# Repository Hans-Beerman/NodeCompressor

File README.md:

**NodeCompressor**

NodeCompressor is a node, used at the MakerSpace Leiden, to control the main compressor. This repository has the following subdirs:

- **Drawings:**

Schematic of the wiring between the different modules used

- **KiCad\_files:**

The design of the PCB for the Node/Controller. De PCB in this design is not meant to be used for a real PCB. It is used as guideline for a handmade PCB

- **Photos:**

Some photos of the Node made.

- **PlatformIO\_Files:**

The source code for the Node and the display used. For the development of this software PlatformIO is used, an Extension on Visual Studio Code.

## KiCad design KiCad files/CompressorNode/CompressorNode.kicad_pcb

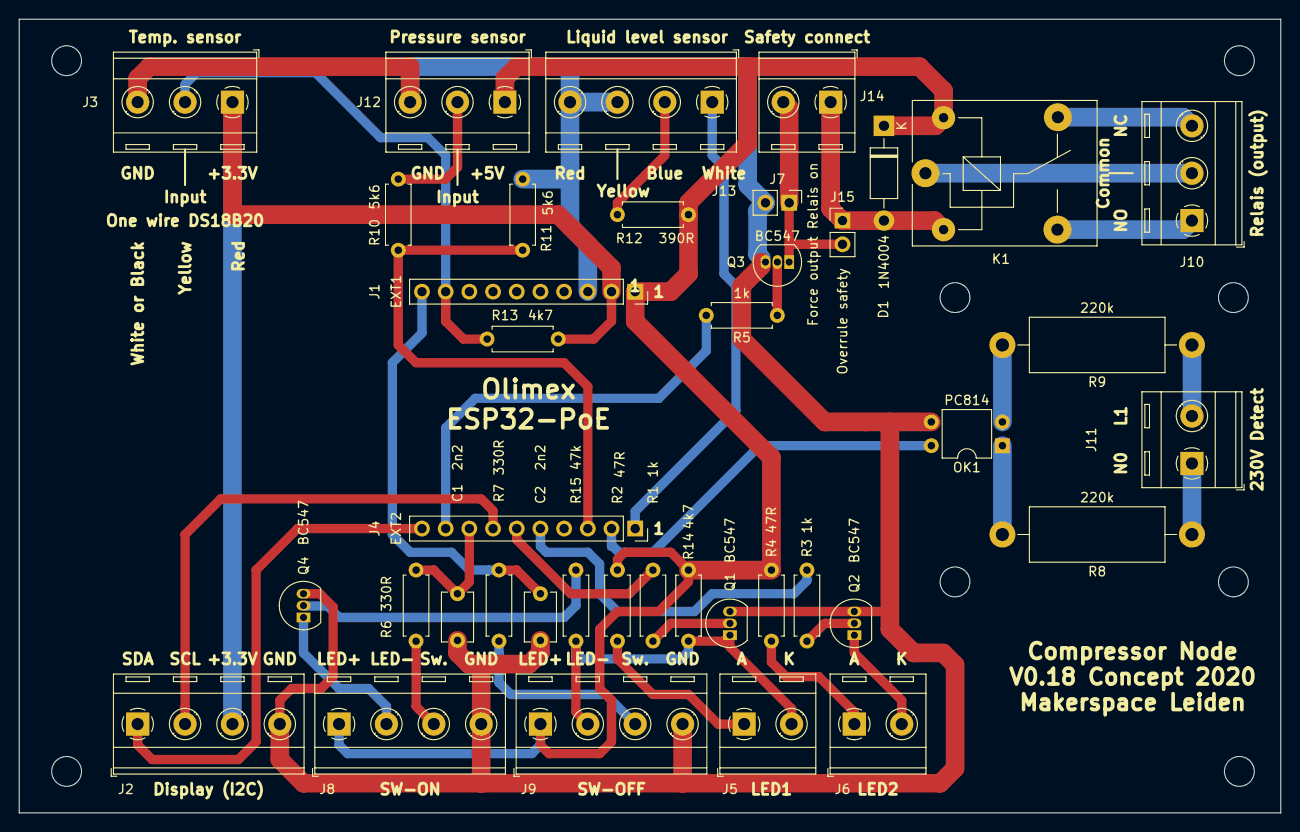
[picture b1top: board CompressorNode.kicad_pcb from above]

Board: 2 copper layers, 135.3 x 85.1 mm, 39 parts (0 on the bottom side), 36 nets.

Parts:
C1, C2: 2n2; C_Disc_D5.1mm_W3.2mm_P5.00mm
D1: 1N4004; D_DO-41_SOD81_P10.16mm_Horizontal
J1: EXT1; PinSocket_1x10_P2.54mm_Vertical
J2, J8, J9, J13: Screw_Terminal_01x04; TerminalBlock_RND_205-00289_1x04_P5.08mm_Horizontal
J3, J10, J12: Screw_Terminal_01x03; TerminalBlock_RND_205-00288_1x03_P5.08mm_Horizontal
J4: EXT2; PinSocket_1x10_P2.54mm_Vertical
J5, J6, J11, J14: Screw_Terminal_01x02; TerminalBlock_RND_205-00287_1x02_P5.08mm_Horizontal
J7: Force output Relais on; PinHeader_1x02_P2.54mm_Vertical
J15: Overrule safety; PinHeader_1x02_P2.54mm_Vertical
K1: SANYOU_SRD_Form_C; Relay_SPDT_SANYOU_SRD_Series_Form_C
OK1: PC814; DIP-4_W7.62mm
Q1, Q2, Q3, Q4: BC547; TO-92_Inline
R1, R3, R5: 1k; R_Axial_DIN0207_L6.3mm_D2.5mm_P7.62mm_Horizontal
R2, R4: 47R; R_Axial_DIN0207_L6.3mm_D2.5mm_P7.62mm_Horizontal
R6, R7: 330R; R_Axial_DIN0207_L6.3mm_D2.5mm_P7.62mm_Horizontal
R8, R9: 220k; R_Axial_DIN0614_L14.3mm_D5.7mm_P20.32mm_Horizontal
R10, R11: 5k6; R_Axial_DIN0207_L6.3mm_D2.5mm_P7.62mm_Horizontal
R12: 390R; R_Axial_DIN0207_L6.3mm_D2.5mm_P7.62mm_Horizontal
R13, R14: 4k7; R_Axial_DIN0207_L6.3mm_D2.5mm_P7.62mm_Horizontal
R15: 47k; R_Axial_DIN0207_L6.3mm_D2.5mm_P7.62mm_Horizontal

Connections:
+3V3: J1.2, J2.3, J3.1, R13.2
+5V: D1.1, J1.1, J8.1, J9.1, J12.1, K1.5, R2.1, R4.1, R12.1, R14.1
GND: C1.2, C2.2, J1.3, J2.4, J3.3, J7.2, J8.4, J9.4, J12.3, J13.3, J13.4, OK1.3, Q1.3, Q2.3, Q3.3, Q4.3, R11.1
GPI35: J4.3, R10.1, R11.2
GPI36_U1RXD: J4.2, OK1.4
GPI39: J4.1, J13.1
GPIO4_U1TXD: J1.9, J3.2, R13.1
GPIO5_SPI_C5: C2.1, J1.10, R7.2
GPIO13_I2C-SDA: J2.1, J4.10
GPIO14_HS2_CLK: J4.9, R5.2
GPIO15_HS2_CMD: C1.1, J4.8, R6.2
GPIO16_I2C-SCL: J2.2, J4.7
GPIO32: J4.6, R1.2
GPIO33: J4.5, R3.2
unnamed: D1.2, J14.1, J15.1, K1.2
unnamed: J5.1, R2.2
unnamed: J6.1, R4.2
unnamed: J6.2, Q2.1
unnamed: J8.2, Q4.1
unnamed: J8.3, R6.1
unnamed: J9.3, R7.1
unnamed: J10.1, K1.3
unnamed: J10.2, K1.1
unnamed: J10.3, K1.4
unnamed: J11.1, R8.1
unnamed: J11.2, R9.1
unnamed: J12.2, R10.2
unnamed: J13.2, R12.2
unnamed: J7.1, J14.2, J15.2, Q3.1
unnamed: OK1.1, R8.2
unnamed: OK1.2, R9.2
unnamed: Q1.2, R1.1
unnamed: Q2.2, R3.1
unnamed: Q3.2, R5.1
unnamed: Q4.2, R15.1
SWITCH-LED1-: J5.2, J9.2, Q1.1, R14.2, R15.2

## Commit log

2020-10-04 first release of complete NodeCompressor project
2020-10-07 Changed the way how the compressor is switched off
2020-10-14 Changed some labels on the display
2020-10-14 changede node name
2020-11-12 V0.18 Concept solved some issues
2021-01-05 V0.19, reboot at 01:00 AM and added automatic extend the automatic timeout time
